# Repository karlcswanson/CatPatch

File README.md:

# CatPatch

This repository contains images and KiCad files for a CAT5e subsnake and DI system.

A brief build log for the DI and breakout cable can be found [here](https://imgur.com/a/OviKR).

## Pinouts
The system, as labeled, is pin-compatible with RAT and ETS audio twisted pair products.  The silkscreen and wiring can be adjusted to make it compatible with other standards.

| RJ45 Pin | [T568B](https://en.wikipedia.org/wiki/TIA/EIA-568#Wiring) | RAT & ETS | Radial & Whirlwind |
|:--------:|:---------------------------------------------------------:|:---------:|:------------------:|
|    1     |                            WO                             |    2+     |         1+         |
|    2     |                             O                             |    2-     |         1-         |
|    3     |                            WG                             |    3+     |         2+         |
|    4     |                             B                             |    1-     |         3+         |
|    5     |                            WB                             |    1+     |         3-         |
|    6     |                             G                             |    3-     |         2-         |
|    7     |                            WBr                            |    4+     |         4+         |
|    8     |                            Br                             |    4-     |         4-         |
---
###### Sources
[RAT CAT Snake](http://www.ratsoundsales.com/mm5/pdf/etherCON_wiring_diagram.pdf) | [Radial Catapult](http://www.radialeng.com/wp-content/uploads/2018/05/Catapult-userguide.pdf) | [Whirlwind Catdusa](http://whirlwindusa.com/media/uploads/catdusa_manual.pdf)

## Cable
Shielded cable is needed when using phantom powered, Clear-Com, and DMX devices over twisted pair.  These devices require pin 1/ground to work. An EtherCON connector does not indicate that a cable is shielded.

Dynamic mics and passive DIs may work without the recommended shield.

## DI
The DI PCB supports the Jensen JT-DB-EPC transformer found in DIs like the Radial JDI. A more affordable transformer can be substituted and can be found in the BOM.

The simplest configuration of the board requires a transformer and 6k81Ω resistor. A stereo summing circuit can be added with a few resistors.  See the [schematic](doc/TSCSnakeDI.pdf) and the [classic RaneNote](https://www.rane.com/note109.html) for more details.

A [drill template](doc/drillguide.pdf) can be found in the docs folder.

Labels can be printed on standard ID cards and can be attached with 3M Command Strip adhesive.
##### Frequency Response

## I just want the boards, how do I get boards?
The boards used for this project are shared at [OSHPARK](https://oshpark.com/profiles/karlcswanson) and can be ordered there.

## BOM
#### Breakout Panel

| Item                                       | Manufacturer | Quantity | Price Each |
|:-------------------------------------------|:-------------|:--------:|-----------:|
| [CH1/10 1U rackmount chassis][1]           | Redco        |    1     |     $66.95 |
| [NE8FDV-B Vertical EtherCON][2]            | Neutrik      |    7     |      $4.17 |
| [NC3MXX-BAG Male XLR][3]                   | Neutrik      |    28    |      $2.96 |
| [SBR Rubber Push-In Grommet 1-3/16" ID][4] | -            |    1     |  $11.80/10 |
| [Neutrik Black Screw for etherCon][5]      | Neutrik      |    14    |       $.21 |
| [Neutrik DBA-BL D blank][6]                | Neutrik      |    1     |       $.73 |
| [Flat Head Screws][7]                      | -            |    2     |   $6.49/50 |
| [Steel Locknut with Lock Washer][8]        | -            |    2     |  $8.72/100 |
| N8FDV breakout PCB                         | Custom       |    7     |          - |

#### DI Box
| Item                                                    | Manufacturer      | Quantity | Price Each |
|:--------------------------------------------------------|:------------------|:--------:|-----------:|
| [Steel Project Box Pre-Punched for 5 D Series XLRs][11] | Pro Speaker Parts |    1     |     $16.65 |
| [NE8FDV-B Vertical EtherCON][2]                         | Neutrik           |    1     |      $4.17 |
| [NC3FD-L-1-BAG Panel mount D XLR][12]                   | Neutirk           |    2     |      $3.22 |
| [NJ3FP6C-BAG Panel mount D TRS][13]                     | Neutrik           |    2     |      $5.76 |
| [JT-DB-EPC Transformer][14]                             | Jensen            |  1 - 2   |     $73.08 |
| __OR__                                                  |                   |          |            |
| [Transformer for PROAV2 and PRODI][15]                  | Radial            |  1 - 2   |     $36.00 |
| [Neutrik Black Screw for etherCon][5]                   | Neutrik           |    2     |       $.21 |
| [Flat Head Screws][7]                                   | -                 |    8     |   $6.49/50 |
| [Steel Locknut with Lock Washer][8]                     | -                 |    8     |  $8.72/100 |
| [Press-Fit Threaded Standoffs][16]                      | -                 |    4     |   $9.14/25 |
| [Button Head Hex Drive Screw][17]                       | -                 |    4     | $11.00/100 |
| N8FDV breakout PCB                                      | Custom            |    1     |          - |
| DI breakout PCB                                         | Custom            |    1     |          - |

[1]: https://www.redco.com/Redco-CH1-10-10-Deep-1U-Rackmount-Chassis.html
[2]: http://www.fullcompass.com/prod/516653-Neutrik-NE8FDV-B
[3]: https://www.redco.com/Neutrik-NC3MXX-BAG.html
[4]: https://www.mcmaster.com/#9600k119/=1cjo0vf
[5]: http://www.fullcompass.com/prod/199358-Neutrik-E-SCREW1-12B
[6]: http://www.neutrik.com/en/xlr/xlr-chassis-connectors-accessories/dba-bl
[7]: https://www.mcmaster.com/#91698a306/=1cjoepo
[8]: https://www.mcmaster.com/#93825a110/=1cjog5u

[11]: https://www.ebay.com/itm/Steel-Project-Box-4-1-2-x-3-3-4-x-1-5-8-Pre-Punched-for-5-D-Series-XLRs/281422391821?hash=item418614ea0d:g:rqUAAOSwxH1T-7Bo
[12]: https://www.redco.com/Neutrik-NC3FD-L-1-BAG.html
[13]: https://www.redco.com/Neutrik-NJ3FP6C-BAG.html
[14]: http://www.jensen-transformers.com/transformers/direct-box/
[15]: http://www.fullcompass.com/prod/279709-Radial-Engineering-R800-9033-00
[16]: https://www.mcmaster.com/#93090a210/=1cjopy9
[17]: https://www.mcmaster.com/#91255a106/=1cjoqt3

## Project Images

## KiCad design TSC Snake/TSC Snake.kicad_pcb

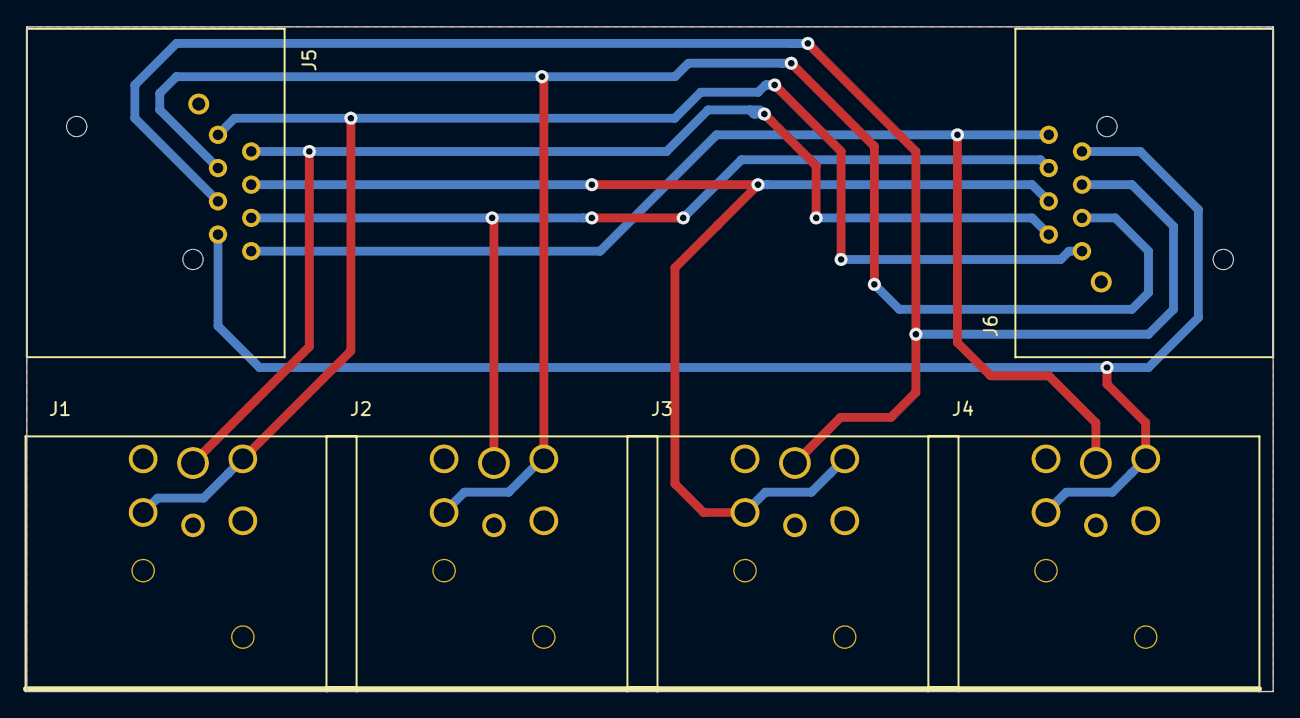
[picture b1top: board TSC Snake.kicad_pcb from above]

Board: 2 copper layers, 95.2 x 50.8 mm, 6 parts (0 on the bottom side), 9 nets.

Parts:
J1, J2, J3, J4: XLR3; NC3FAH-NC3MAH
J5, J6: RJ45; NE8FAH-C5

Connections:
GND: J1.1, J2.1, J3.1, J4.1
unnamed: J1.2, J5.1, J6.1
unnamed: J1.3, J5.2, J6.2
unnamed: J2.2, J5.3, J6.3
unnamed: J2.3, J5.6, J6.6
unnamed: J3.2, J5.4, J6.4
unnamed: J3.3, J5.5, J6.5
unnamed: J4.2, J5.7, J6.7
unnamed: J4.3, J5.8, J6.8

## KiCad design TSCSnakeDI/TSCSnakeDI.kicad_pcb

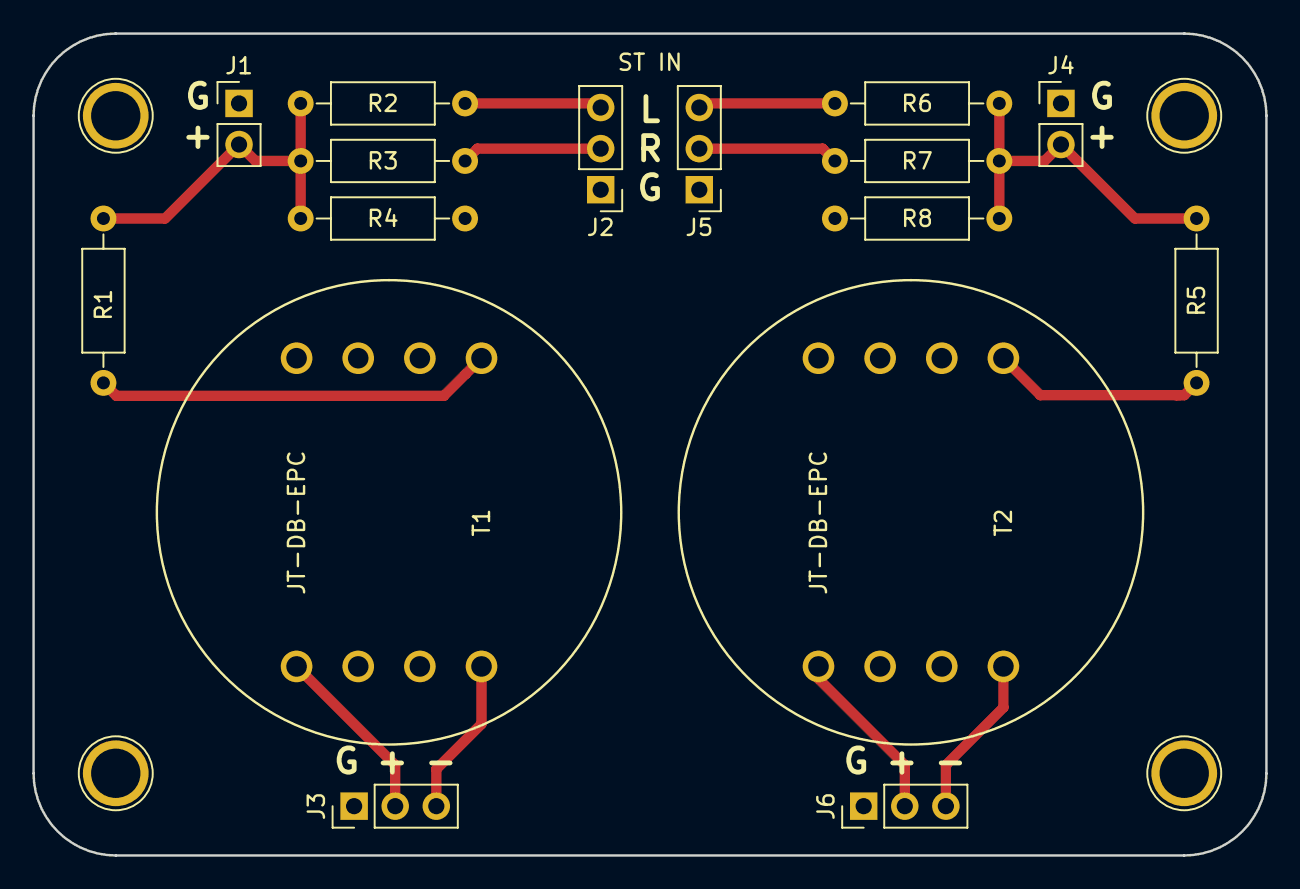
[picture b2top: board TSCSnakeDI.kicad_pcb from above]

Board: 2 copper layers, 76.2 x 50.8 mm, 16 parts (0 on the bottom side), 13 nets.

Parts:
J1: CH 1 IN; Pin_Header_Straight_1x02_Pitch2.54mm
J2, J5: ST IN; Pin_Header_Straight_1x03_Pitch2.54mm
J3: CH 1 OUT; Pin_Header_Straight_1x03_Pitch2.54mm
J4: CH 2 IN; Pin_Header_Straight_1x02_Pitch2.54mm
J6: CH 2 OUT; Pin_Header_Straight_1x03_Pitch2.54mm
R1, R5: 6k81; R_Axial_DIN0207_L6.3mm_D2.5mm_P10.16mm_Horizontal
R2, R3, R6, R7: 475; R_Axial_DIN0207_L6.3mm_D2.5mm_P10.16mm_Horizontal
R4, R8: 20k; R_Axial_DIN0207_L6.3mm_D2.5mm_P10.16mm_Horizontal
T1, T2: JT-DB-EPC

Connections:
GND: J1.1, J2.1, J3.1, J4.1, J5.1, J6.1, R4.1, R8.1, T1.3, T1.6, T1.7, T1.8, T2.3, T2.6, T2.7, T2.8
unnamed: J1.2, R1.2, R2.1, R3.1, R4.2
unnamed: J2.2, R3.2
unnamed: J2.3, R2.2
unnamed: J3.2, T1.1
unnamed: J3.3, T1.4
unnamed: J4.2, R5.2, R6.1, R7.1, R8.2
unnamed: J5.2, R7.2
unnamed: J5.3, R6.2
unnamed: J6.2, T2.1
unnamed: J6.3, T2.4
unnamed: R1.1, T1.5
unnamed: R5.1, T2.5

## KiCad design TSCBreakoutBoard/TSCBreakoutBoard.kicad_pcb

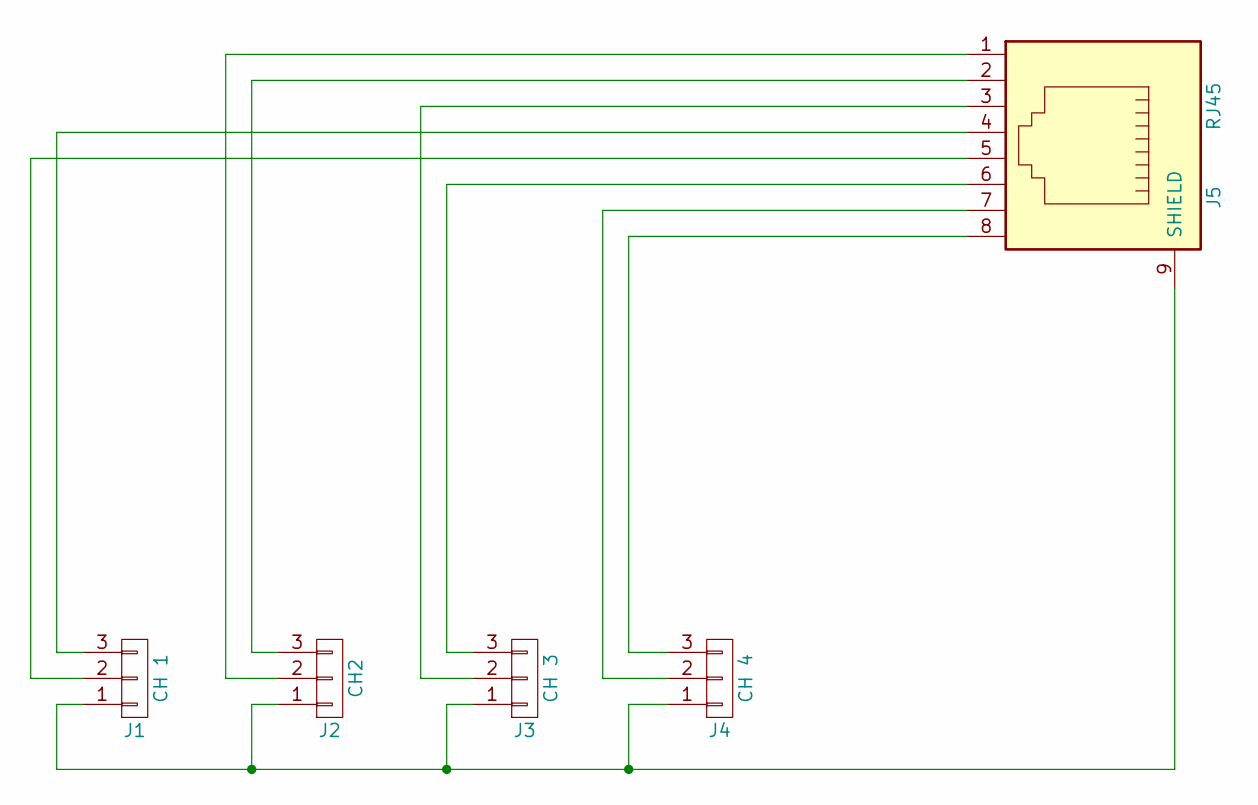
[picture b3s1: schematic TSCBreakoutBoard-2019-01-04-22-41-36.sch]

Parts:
J1: CH 1; Pin_Header_Straight_1x03_Pitch2.54mm
J2: CH2; Pin_Header_Straight_1x03_Pitch2.54mm
J3: CH 3; Pin_Header_Straight_1x03_Pitch2.54mm
J4: CH 4; Pin_Header_Straight_1x03_Pitch2.54mm
J5: RJ45; NE8FDV

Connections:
unnamed: J1.1, J2.1, J3.1, J4.1, J5.9 (SHIELD)
unnamed: J1.2, J5.5
unnamed: J1.3, J5.4
unnamed: J2.2, J5.1
unnamed: J2.3, J5.2
unnamed: J3.2, J5.3
unnamed: J3.3, J5.6
unnamed: J4.2, J5.7
unnamed: J4.3, J5.8

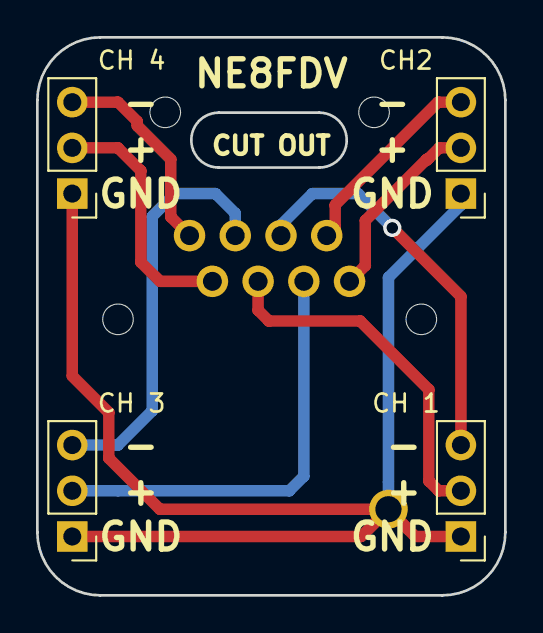
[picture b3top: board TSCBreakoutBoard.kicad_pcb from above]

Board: 2 copper layers, 26.0 x 31.0 mm, 5 parts (0 on the bottom side), 9 nets.

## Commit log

2018-04-18 Initial Commit
    Initial Commit!
2018-04-18 Git ignore
2018-04-23 remove logo & date
2018-04-23 remove logo, relative paths
2018-04-23 remove logo & old breakout PCB
2018-04-23 adjust paths
2018-04-23 Additional path updates
2018-04-23 Remove logo & link DI PCB
2018-04-23 Add drill guide
2018-04-23 Add README.md
2018-04-23 Additional readme
2018-04-24 Update BOM
2019-01-20 doc update
2019-01-20 rdme
2019-01-20 pcbb
2019-01-20 readme
